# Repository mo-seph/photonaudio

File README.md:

# Quad LED Driver: audio over light

A four-channel analog LED driver for sending audio-rate signals through the air as light: soundcard → LED → air → phototransistor pickup → soundcard. Each channel is a linear voltage-controlled current sink (op-amp, transistor, sense resistor), so the light follows the signal rather than the LED's exponential V/I curve. Audio rides on an idle brightness set per channel by an on-board DAC or a trimmer. The design clips cleanly at off and at full when the input is overdriven, and the op-amp's supply rail sets a hard ceiling on LED current.

*Quad LED Driver Board v1.0 (November 2026): 170 × 100 mm, two layers. On the left is the 12 V input, the 5 V and 3.3 V supplies, and a XIAO ESP32-S3 with an MCP4728 four-channel DAC for the idle brightness. On the right are four identical channels A–D, each with a balanced audio input, DC lift, bias select (DAC or trimmer), amplifier, current sink and LED output.*

*The routing: top copper in red, bottom copper in blue, with the silkscreen. Each channel's current-sense return runs back separately to the star point at the main capacitor (the four diagonal tracks at bottom centre).*

## Status

- **v1.0 boards** arrived on 2026-11-17. Channel A, the supplies and the DAC are built and working, and channels B–D are next.
- **Channel A, measured** over a bench optical link (`measure/`): about 67 dB SNR unweighted (69 dB(A)) at 1% THD, with a −3 dB bandwidth of about 67 Hz to 20 kHz. The limit is the photosensor's distortion, not the driver.

## What's here

| Path | Contents |
|---|---|
| [OVERVIEW.md](OVERVIEW.md) | Goals and approach |
| [TUTORIAL.md](TUTORIAL.md) | How one channel works, part by part, with figures in `tutorial/` |
| [WORKING.md](WORKING.md) | Design notes, schematic and board reviews, measurement and bring-up log |
| [BRINGUP.md](BRINGUP.md) | Breadboard bring-up of one channel, power, XIAO and DAC |
| [build_plan/](build_plan/) | Staged build-and-test guide for the PCB (`index.html`, generated by `make_page.py`) |
| [BOM_pcb.md](BOM_pcb.md), [BOM_breadboard.md](BOM_breadboard.md) | Parts lists |
| [schematics/](schematics/) | Fusion Electronics (Eagle format) schematics and boards, PDF prints, and circuit drawings (`channel.png`, `dac.png`, `power.png`, `supply_filter.png`) |
| [cam_output/](cam_output/) | Gerbers as sent to JLCPCB for v1.0 |
| [fab/jlcpcb/](fab/jlcpcb/) | JLCPCB's CAM job and design rules for Fusion |
| [kicad/](kicad/) | The board converted to KiCad 10, checked against the Fusion original |
| [dac_test/](dac_test/) | Test firmware (PlatformIO) for the MCP4728 bias DAC |
| [measure/](measure/) | `linkmeasure`: frequency response, noise and distortion of the optical link, with every run's results |

In normal use, the board joins an I2C network of ESP32 devices as a Peripheral, with the four LED channels as one Element. That firmware lives in a separate repository.

Raw audio recordings from the measurements are not in the repository; each run keeps its analysed results (CSV, PNG, JSON).

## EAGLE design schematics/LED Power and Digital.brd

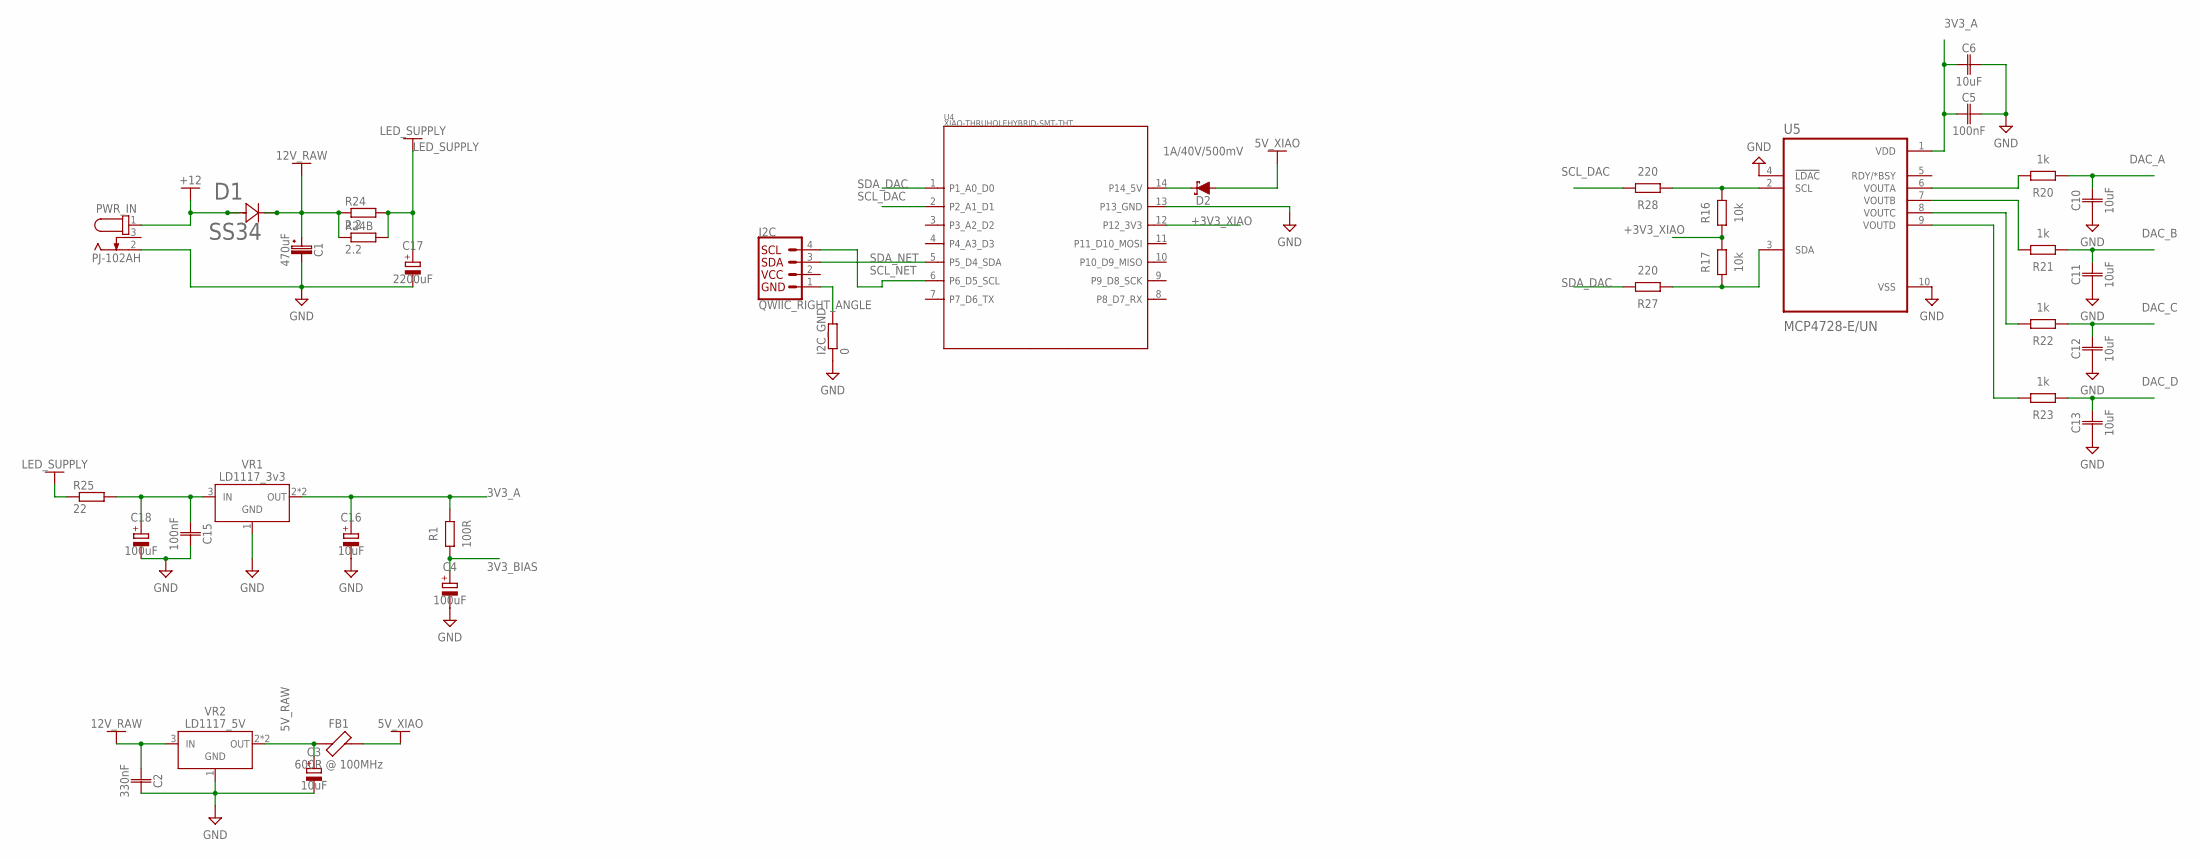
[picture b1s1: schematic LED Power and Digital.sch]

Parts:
C1: 470uF; CAPAE1030X1050N
C2: 330nF; CAPC2012X110
C3, C16: 10uF; A/3216-18W
C4, C18: 100uF; 153CLV-0605
C5, C15: 100nF; CAPC2012X110
C6, C10, C11, C12, C13: 10uF; CAPC3216X135
C17: 2200uF; E7,5-16
D1: SS34; DIODE_DO214AB
D2: 1A/40V/500mV; SMA-DIODE
FB1: 600R @ 100MHz; BEADC2012X105N
I2C: QWIIC_RIGHT_ANGLE; JST04_1MM_RA
I2C_GND: 0; R0805
PWR_IN: PJ-102AH
R1: 100R; RESC3216X70
R16, R17: 10k; RESC3216X70
R20, R21, R22, R23: 1k; RESC3216X70
R24, R24B: 2.2; R2512
R25: 22; R0805
R27, R28: 220; RESC3216X70
U4: XIAO-THRUHOLEHYBRID-SMT-THT; XIAO-GENERIC-HYBRID-MODULE14P-2.54-21X17.8MM
U5: MCP4728-E/UN; SOP50P490X110-10N
VR1: LD1117_3v3; SOT230P700X170-4
VR2: LD1117_5V; SOT230P700X170-4

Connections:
2: I2C.2
3V3_A: C5.1, C6.1, C16.+, R1.2, U5.1 (VDD), VR1.2 (VO), VR1.4 (VO)
3V3_BIAS: C4.+, R1.1
5V_RAW: C3.+, FB1.1, VR2.2 (VO), VR2.4 (VO)
5V_XIAO: D2.A, FB1.2
12V_RAW: C1.1 (+), C2.1, D1.1, R24.1, R24B.1, VR2.3 (VI); also elsewhere on the board
+3V3_XIAO: R16.1, R17.2, U4.12 (P12_3V3)
+12: D1.2, PWR_IN.1; also elsewhere on the board
DAC_A: C10.2, R20.1
DAC_B: C11.2, R21.1
DAC_C: C12.2, R22.1
DAC_D: C13.2, R23.1
GND: C1.2 (-), C2.2, C3.-, C4.-, C5.2, C6.2, C10.1, C11.1, C12.1, C13.1, C15.2, C16.-, C17.-, C18.-, I2C_GND.1, PWR_IN.2, U4.13 (P13_GND), U5.4 (!LDAC), U5.10 (VSS), VR1.1 (GND), VR2.1 (GND)
LED_SUPPLY: C17.+, R24.2, R24B.2, R25.1
unnamed: D2.C, U4.14 (P14_5V)
unnamed: I2C.1, I2C_GND.2
unnamed: C15.1, C18.+, R25.2, VR1.3 (VI)
unnamed: R16.2, R28.1, U5.2 (SCL)
unnamed: R17.1, R27.1, U5.3 (SDA)
unnamed: R20.2, U5.6 (VOUTA)
unnamed: R21.2, U5.7 (VOUTB)
unnamed: R22.2, U5.8 (VOUTC)
unnamed: R23.2, U5.9 (VOUTD)
SCL_DAC: R28.2, U4.2 (P2_A1_D1)
SCL_NET: I2C.4, U4.6 (P6_D5_SCL)
SDA_DAC: R27.2, U4.1 (P1_A0_D0)
SDA_NET: I2C.3, U4.5 (P5_D4_SDA)

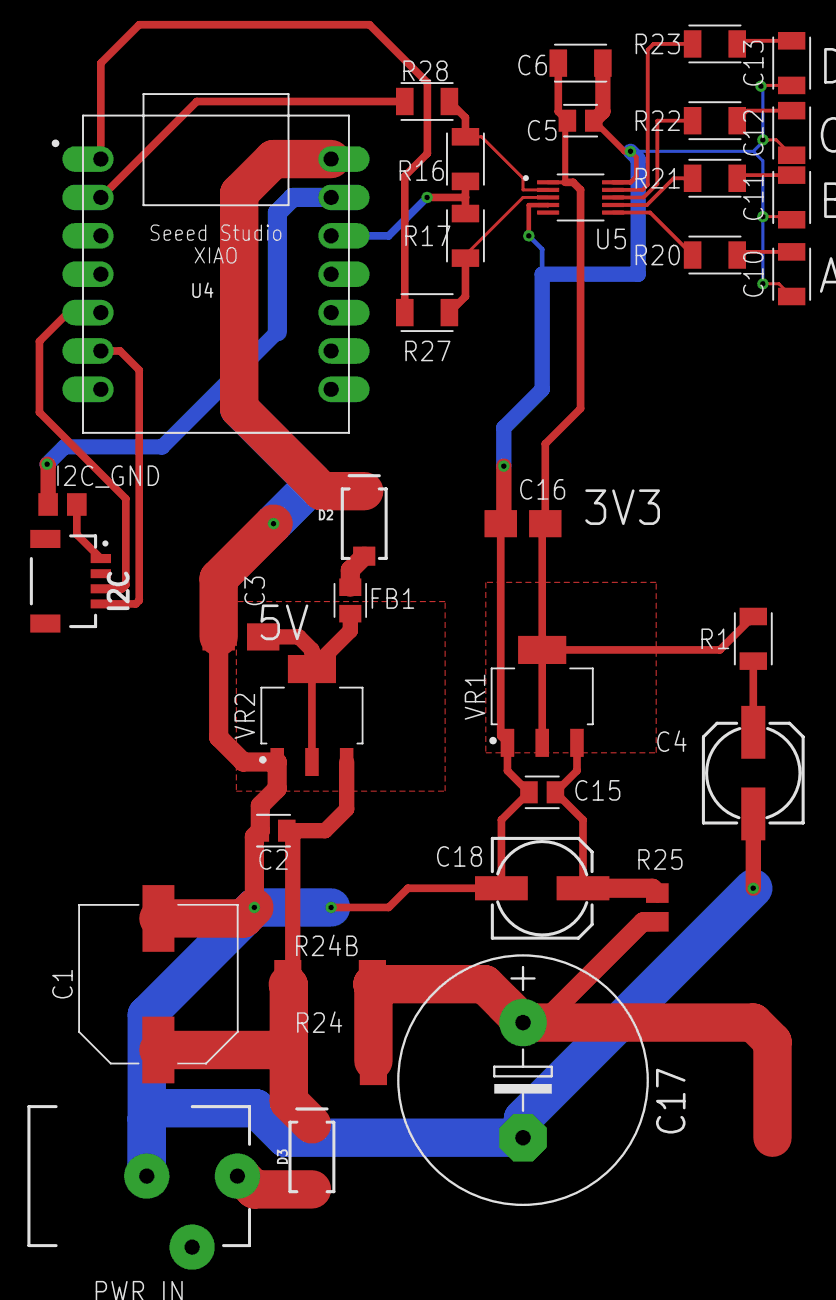
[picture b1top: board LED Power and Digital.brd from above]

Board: 2 copper layers, 36 parts (0 on the bottom side), 26 nets.

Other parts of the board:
D3: 3A/40V/500mV; SMA-DIODE

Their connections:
12V_RAW: D3.C; also elsewhere on the board
+12: D3.A; also elsewhere on the board

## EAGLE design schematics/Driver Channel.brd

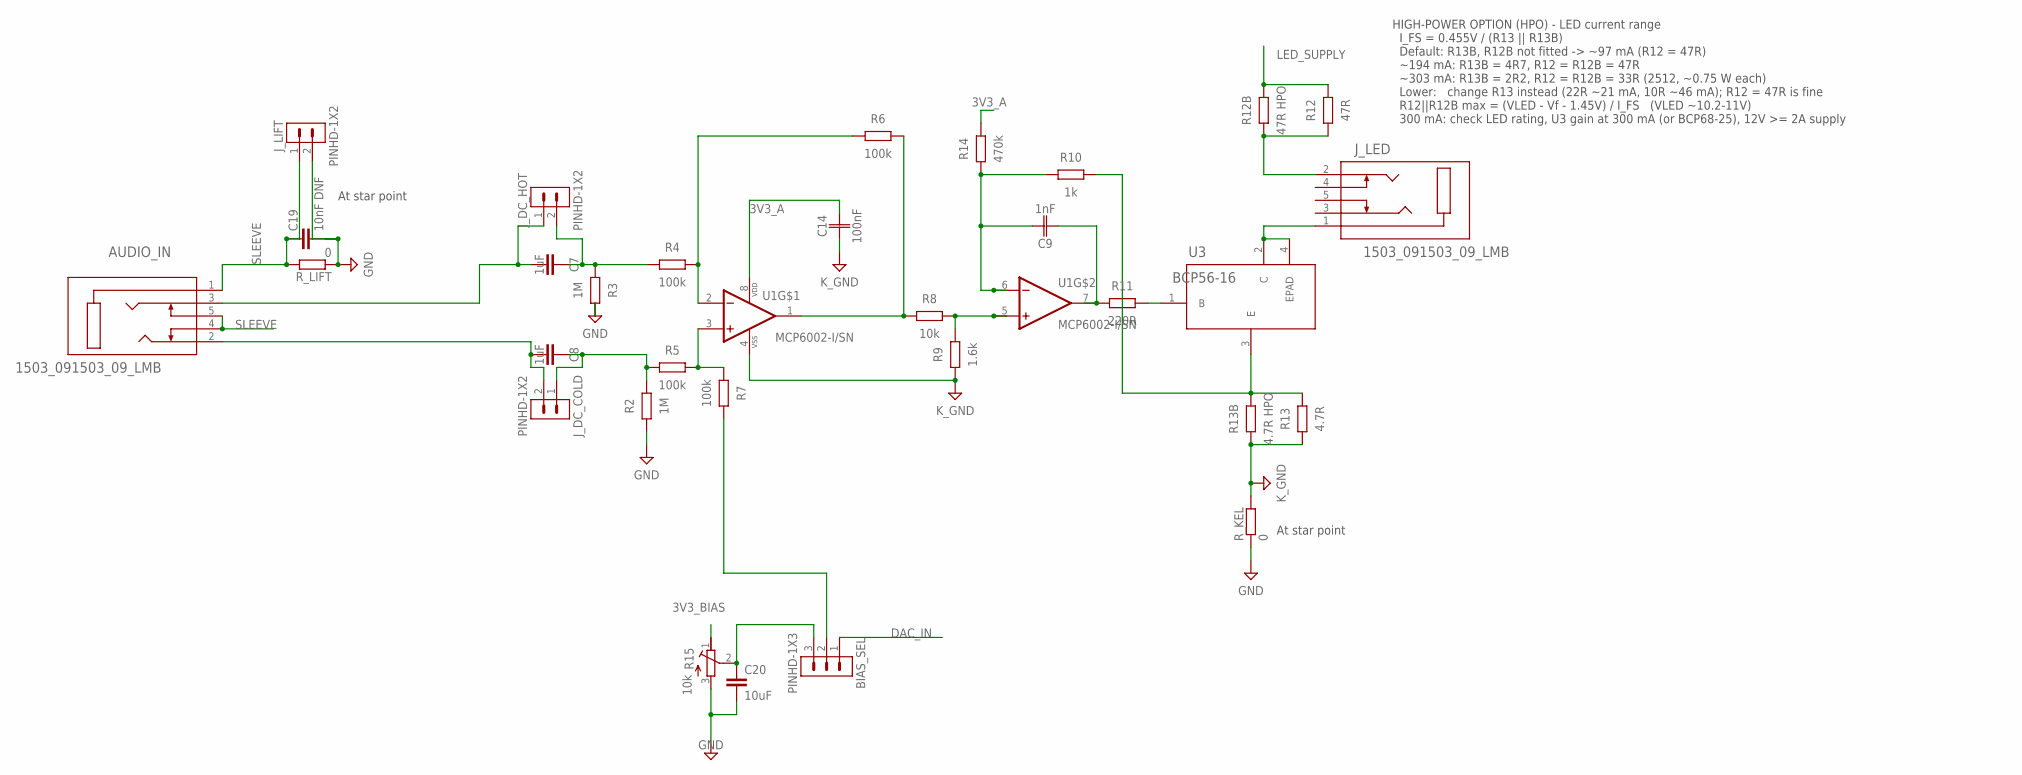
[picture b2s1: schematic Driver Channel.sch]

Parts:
AUDIO_IN: 1503_091503_09_LMB; 1503_09_LMB
BIAS_SEL: PINHD-1X3; 1X03
C7, C8: 1uF; C0805
C9: 1nF; CAPC2012X110
C14: 100nF; CAPC2012X110
C19: 10nF DNF; C0805
C20: 10uF; C0805
J_DC_COLD: PINHD-1X2; 1X02
J_DC_HOT: PINHD-1X2; 1X02
J_LED: 1503_091503_09_LMB; 1503_09_LMB
J_LIFT: PINHD-1X2; 1X02
R2, R3: 1M; RESC3216X70
R4, R5, R6, R7: 100k; RESC3216X70
R8: 10k; RESC3216X70
R9: 1.6k; RESC3216X70
R10: 1k; RESC3216X70
R11: 220R; RESC3216X70
R12: 47R; RESC6332X71
R12B: 47R HPO; RESC6332X71
R13: 4.7R; RESC3216X70
R13B: 4.7R HPO; RESC3216X70
R14: 470k; RESC3216X70
R15: 10k; RTRIM3314J
R_KEL: 0; R0805
R_LIFT: 0; R0805
U1: MCP6002-I/SN; SOIC127P600X175-8N
U3: BCP56-16; SOT-223_3P7X6P7_ONS

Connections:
3V3_A: C14.2, R14.2, U1.8 (VDD)
3V3_BIAS: R15.1 (E)
DAC_IN: BIAS_SEL.1
GND: C19.2, C20.2, J_LIFT.2, R2.1, R3.2, R15.3 (A), R_KEL.1, R_LIFT.1
K_GND: C14.1, R9.1, R13.1, R13B.1, R_KEL.2, U1.4 (VSS)
LED_SUPPLY: R12.2, R12B.2
unnamed: C8.1, J_DC_COLD.1, R2.2, R5.1
unnamed: C7.1, J_DC_HOT.2, R3.1, R4.1
unnamed: R4.2, R6.1, U1.2 (VINA-)
unnamed: R5.2, R7.1, U1.3 (VINA+)
unnamed: R6.2, R8.1, U1.1 (VOUTA)
unnamed: R8.2, R9.2, U1.5 (VINB+)
unnamed: R11.2, U3.1 (B)
unnamed: J_LED.1, U3.2 (C), U3.4 (EPAD)
unnamed: J_LED.2, R12.1, R12B.1
unnamed: R10.2, R13.2, R13B.2, U3.3 (E)
unnamed: C9.1, R11.1, U1.7 (VOUTB)
unnamed: C9.2, R10.1, R14.1, U1.6 (VINB-)
unnamed: BIAS_SEL.3, C20.1, R15.2 (S)
unnamed: AUDIO_IN.2, C8.2, J_DC_COLD.2
unnamed: AUDIO_IN.3, C7.2, J_DC_HOT.1
unnamed: BIAS_SEL.2, R7.2
SLEEVE: AUDIO_IN.1, AUDIO_IN.4, AUDIO_IN.5, C19.1, J_LIFT.1, R_LIFT.2

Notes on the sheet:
At star point
HIGH-POWER OPTION (HPO) - LED current range I_FS = 0.455V / (R13 || R13B) Default: R13B, R12B not fitted -> ~97 mA (R12 = 47R) ~194 mA: R13B = 4R7, R12 = R12B = 47R ~303 mA: R13B = 2R2, R12 = R12B = 33R (2512, ~0.75 W each) Lower: change R13 instead (22R ~21 mA, 10R ~46 mA); R12 = 47R is fine R12||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

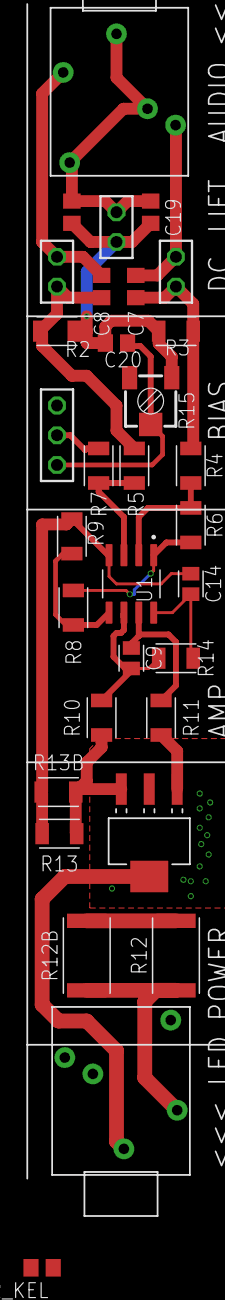
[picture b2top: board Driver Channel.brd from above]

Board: 2 copper layers, 32 parts (0 on the bottom side), 21 nets.

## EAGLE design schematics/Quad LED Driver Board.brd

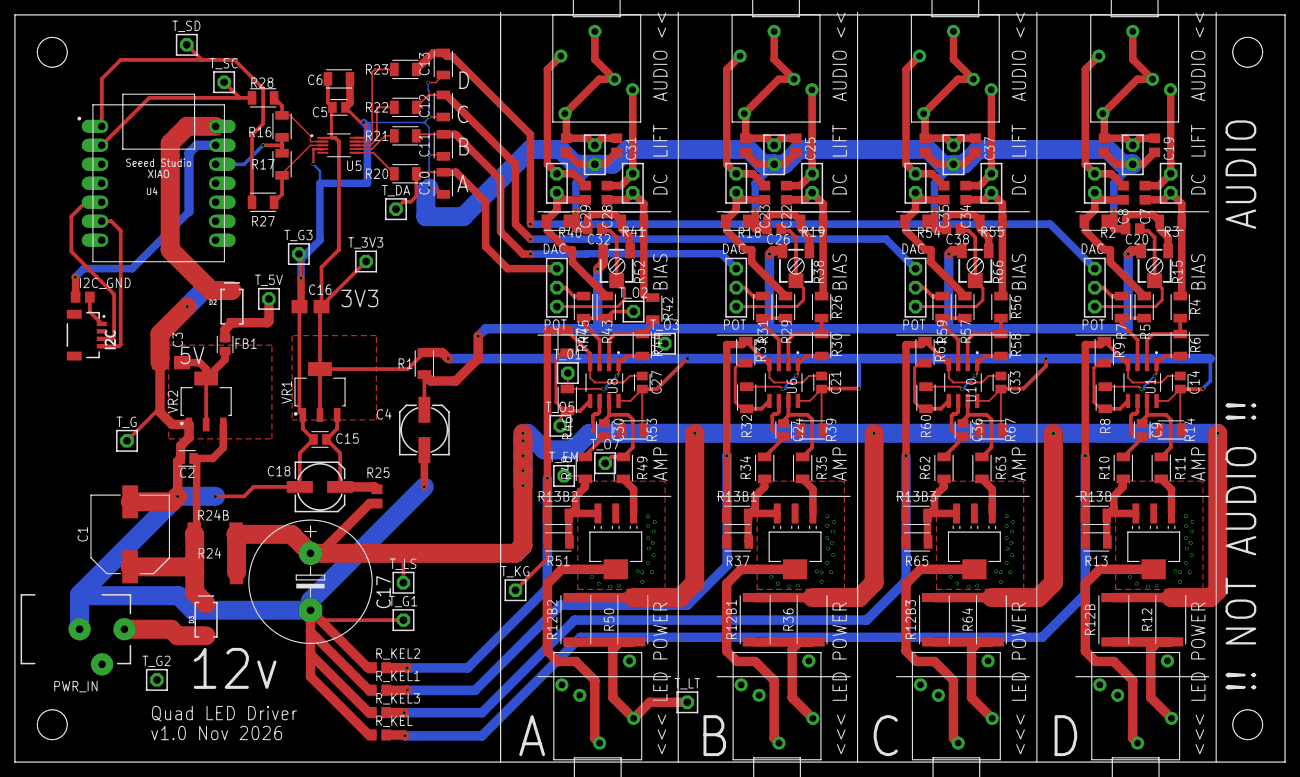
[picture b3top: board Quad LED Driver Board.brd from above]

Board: 2 copper layers, 170.0 x 100.0 mm, 182 parts (0 on the bottom side), 98 nets.

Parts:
AUDIO_IN, AUDIO_IN1, AUDIO_IN2, AUDIO_IN3: 1503_091503_09_LMB; 1503_09_LMB
BIAS_SEL, BIAS_SEL1, BIAS_SEL2, BIAS_SEL3: PINHD-1X3; 1X03
C1: 470uF; CAPAE1030X1050N
C2: 330nF; CAPC2012X110
C3, C16: 10uF; A/3216-18W
C4, C18: 100uF; 153CLV-0605
C5, C14, C15, C21, C27, C33: 100nF; CAPC2012X110
C6, C10, C11, C12, C13: 10uF; CAPC3216X135
C7, C8, C22, C23, C28, C29, C34, C35: 1uF; C0805
C9, C24, C30, C36: 1nF; CAPC2012X110
C17: 2200uF; E7,5-16
C19, C25, C31, C37: 10nF DNF; C0805
C20, C26, C32, C38: 10uF; C0805
D2: 1A/40V/500mV; SMA-DIODE
D3: 3A/40V/500mV; SMA-DIODE
FB1: 600R @ 100MHz; BEADC2012X105N
I2C: QWIIC_RIGHT_ANGLE; JST04_1MM_RA
I2C_GND: 0; R0805
J_DC_COLD, J_DC_COLD1, J_DC_COLD2, J_DC_COLD3: PINHD-1X2; 1X02
J_DC_HOT, J_DC_HOT1, J_DC_HOT2, J_DC_HOT3: PINHD-1X2; 1X02
J_LED, J_LED1, J_LED2, J_LED3: 1503_091503_09_LMB; 1503_09_LMB
J_LIFT, J_LIFT1, J_LIFT2, J_LIFT3: PINHD-1X2; 1X02
PWR_IN: PJ-102AH
R1: 100R; RESC3216X70
R2, R3, R18, R19, R40, R41, R54, R55: 1M; RESC3216X70
R4, R5, R6, R7, R26, R29, R30, R31, R42, R43, R44, R45, R56, R57, R58, R59: 100k; RESC3216X70
R8, R16, R17, R32, R46, R60: 10k; RESC3216X70
R9, R33, R47, R61: 1.6k; RESC3216X70
R10, R20, R21, R22, R23, R34, R48, R62: 1k; RESC3216X70
R11, R35, R49, R63: 220R; RESC3216X70
R12, R36, R50, R64: 47R; RESC6332X71
R12B, R12B1, R12B2, R12B3: 47R HPO; RESC6332X71
R13, R37, R51, R65: 4.7R; RESC3216X70
R13B, R13B1, R13B2, R13B3: 4.7R HPO; RESC3216X70
R14, R39, R53, R67: 470k; RESC3216X70
R15, R38, R52, R66: 10k; RTRIM3314J
R24, R24B: 2.2; R2512
R25: 22; R0805
R27, R28: 220; RESC3216X70
R_KEL, R_KEL1, R_KEL2, R_KEL3: 0; R0805
R_LIFT, R_LIFT1, R_LIFT2, R_LIFT3: 0; R0805
T_01, T_3V3, T_5V: PINHD-1X1; 1X01
T_DA: PINHD-1X1; 1X01
T_EM: PINHD-1X1; 1X01
T_G, T_G1, T_G2, T_G3: PINHD-1X1; 1X01
T_KG: PINHD-1X1; 1X01
T_LS: PINHD-1X1; 1X01
T_LT: PINHD-1X1; 1X01
T_O2, T_O3, T_O5, T_O7: PINHD-1X1; 1X01
T_SC: PINHD-1X1; 1X01
T_SD: PINHD-1X1; 1X01
U1, U6, U8, U10: MCP6002-I/SN; SOIC127P600X175-8N
U2, U3, U7, U9: BCP56-16; SOT-223_3P7X6P7_ONS
U4: XIAO-THRUHOLEHYBRID-SMT-THT; XIAO-GENERIC-HYBRID-MODULE14P-2.54-21X17.8MM
U5: MCP4728-E/UN; SOP50P490X110-10N
VR1: LD1117_3v3; SOT230P700X170-4
VR2: LD1117_5V; SOT230P700X170-4

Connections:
3V3_A: C5.1, C6.1, C14.2, C16.+, C21.2, C27.2, C33.2, R1.2, R14.2, R39.2, R53.2, R67.2, T_3V3.1, U1.8, U5.1, U6.8, U8.8, U10.8, VR1.2, VR1.4
3V3_BIAS: C4.+, R1.1, R15.1, R38.1, R52.1, R66.1
5V_RAW: C3.+, FB1.1, VR2.2, VR2.4
5V_XIAO: D2.A, FB1.2, T_5V.1
12V_RAW: C1.1, C2.1, D3.C, R24.1, R24B.1, VR2.3
+3V3_XIAO: R16.1, R17.2, U4.12
+12: D3.A, PWR_IN.1
DAC_A: BIAS_SEL2.1, C10.2, R20.1, T_DA.1
DAC_B: BIAS_SEL1.1, C11.2, R21.1
DAC_C: BIAS_SEL3.1, C12.2, R22.1
DAC_D: BIAS_SEL.1, C13.2, R23.1
GND: C1.2, C2.2, C3.-, C4.-, C5.2, C6.2, C10.1, C11.1, C12.1, C13.1, C15.2, C16.-, C17.-, C18.-, C19.2, C20.2, C25.2, C26.2, C31.2, C32.2, C37.2, C38.2, I2C_GND.1, J_LIFT.2, J_LIFT1.2, J_LIFT2.2, J_LIFT3.2, PWR_IN.2, R2.1, R3.2, R15.3, R18.1, R19.2, R38.3, R40.1, R41.2, R52.3, R54.1, R55.2, R66.3, R_KEL.1, R_KEL1.1, R_KEL2.1, R_KEL3.1, R_LIFT.1, R_LIFT1.1, R_LIFT2.1, R_LIFT3.1, T_G.1, T_G1.1, T_G2.1, T_G3.1, U4.13, U5.4, U5.10, VR1.1, VR2.1
K_GND_A: C27.1, R13B2.1, R47.1, R51.1, R_KEL2.2, T_KG.1, U8.4
K_GND_B: C21.1, R13B1.1, R33.1, R37.1, R_KEL1.2, U6.4
K_GND_C: C33.1, R13B3.1, R61.1, R65.1, R_KEL3.2, U10.4
K_GND_D: C14.1, R9.1, R13.1, R13B.1, R_KEL.2, U1.4
LED_SUPPLY: C17.+, R12.2, R12B.2, R12B1.2, R12B2.2, R12B3.2, R24.2, R24B.2, R25.1, R36.2, R50.2, R64.2, T_LS.1
unnamed: D2.C, U4.14
unnamed: I2C.1, I2C_GND.2
unnamed: C15.1, C18.+, R25.2, VR1.3
unnamed: C8.1, J_DC_COLD.1, R2.2, R5.1
unnamed: C7.1, J_DC_HOT.2, R3.1, R4.1
unnamed: R4.2, R6.1, U1.2
unnamed: R5.2, R7.1, U1.3
unnamed: R6.2, R8.1, U1.1
unnamed: R8.2, R9.2, U1.5
unnamed: R11.2, U3.1
unnamed: J_LED.2, R12.1, R12B.1
unnamed: R10.2, R13.2, R13B.2, U3.3
unnamed: C9.1, R11.1, U1.7
unnamed: C9.2, R10.1, R14.1, U1.6
unnamed: AUDIO_IN.2, C8.2, J_DC_COLD.2
unnamed: BIAS_SEL.2, R7.2
unnamed: AUDIO_IN.3, C7.2, J_DC_HOT.1
unnamed: BIAS_SEL.3, C20.1, R15.2
unnamed: J_LED.1, U3.4
unnamed: C23.1, J_DC_COLD1.1, R18.2, R29.1
unnamed: R16.2, R28.1, U5.2
unnamed: R17.1, R27.1, U5.3
unnamed: R20.2, U5.6
unnamed: R21.2, U5.7
unnamed: R22.2, U5.8
unnamed: R23.2, U5.9
unnamed: C22.1, J_DC_HOT1.2, R19.1, R26.1
unnamed: R26.2, R30.1, U6.2
unnamed: R29.2, R31.1, U6.3
unnamed: R30.2, R32.1, U6.1
unnamed: R32.2, R33.2, U6.5
unnamed: R35.2, U2.1
unnamed: J_LED1.2, R12B1.1, R36.1
unnamed: R13B1.2, R34.2, R37.2, U2.3
unnamed: C24.1, R35.1, U6.7
unnamed: C24.2, R34.1, R39.1, U6.6
unnamed: AUDIO_IN1.2, C23.2, J_DC_COLD1.2
unnamed: BIAS_SEL1.2, R31.2
unnamed: AUDIO_IN1.3, C22.2, J_DC_HOT1.1
unnamed: BIAS_SEL1.3, C26.1, R38.2
unnamed: J_LED1.1, U2.4
unnamed: C29.1, J_DC_COLD2.1, R40.2, R43.1
unnamed: C28.1, J_DC_HOT2.2, R41.1, R42.1
unnamed: R42.2, R44.1, T_O3.1, U8.2
unnamed: R43.2, R45.1, T_O2.1, U8.3
unnamed: R44.2, R46.1, T_01.1, U8.1
unnamed: R46.2, R47.2, T_O5.1, U8.5
unnamed: R49.2, U7.1
unnamed: J_LED2.2, R12B2.1, R50.1, T_LT.1
unnamed: R13B2.2, R48.2, R51.2, T_EM.1, U7.3
unnamed: C30.1, R49.1, T_O7.1, U8.7
unnamed: C30.2, R48.1, R53.1, U8.6
unnamed: AUDIO_IN2.2, C29.2, J_DC_COLD2.2
unnamed: BIAS_SEL2.2, R45.2
unnamed: AUDIO_IN2.3, C28.2, J_DC_HOT2.1
unnamed: BIAS_SEL2.3, C32.1, R52.2
unnamed: J_LED2.1, U7.4
unnamed: C35.1, J_DC_COLD3.1, R54.2, R57.1
unnamed: C34.1, J_DC_HOT3.2, R55.1, R56.1
unnamed: R56.2, R58.1, U10.2
unnamed: R57.2, R59.1, U10.3
unnamed: R58.2, R60.1, U10.1
unnamed: R60.2, R61.2, U10.5
unnamed: R63.2, U9.1
unnamed: J_LED3.2, R12B3.1, R64.1
unnamed: R13B3.2, R62.2, R65.2, U9.3
unnamed: C36.1, R63.1, U10.7
unnamed: C36.2, R62.1, R67.1, U10.6
unnamed: AUDIO_IN3.2, C35.2, J_DC_COLD3.2
unnamed: BIAS_SEL3.2, R59.2
unnamed: AUDIO_IN3.3, C34.2, J_DC_HOT3.1
unnamed: BIAS_SEL3.3, C38.1, R66.2
unnamed: J_LED3.1, U9.4
SCL_DAC: R28.2, T_SC.1, U4.2
SCL_NET: I2C.4, U4.6
SDA_DAC: R27.2, T_SD.1, U4.1
SDA_NET: I2C.3, U4.5
SLEEVE_A: AUDIO_IN2.1, AUDIO_IN2.4, AUDIO_IN2.5, C31.1, J_LIFT2.1, R_LIFT2.2
SLEEVE_B: AUDIO_IN1.1, AUDIO_IN1.4, AUDIO_IN1.5, C25.1, J_LIFT1.1, R_LIFT1.2
SLEEVE_C: AUDIO_IN3.1, AUDIO_IN3.4, AUDIO_IN3.5, C37.1, J_LIFT3.1, R_LIFT3.2
SLEEVE_D: AUDIO_IN.1, AUDIO_IN.4, AUDIO_IN.5, C19.1, J_LIFT.1, R_LIFT.2

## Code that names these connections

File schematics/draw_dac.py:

"""DAC section, 3.3 V analog version (2026-10-23): XIAO + MCP4728 + output smoothing.
The DAC runs from +3V3_A, so it talks to the XIAO directly - no level shifter (Q2, Q3, R18, R19 removed;
R16/R17 stay as the 4.7k bus pull-ups).
Designators follow 'LED Driver.sch'. BIAS_SEL pin 1 <- DAC_x is the intended wiring.
Power rails are shown as net labels (open dots) rather than drawn wires.
v1 (2026-11-04, from the DAC update-noise tests; new / changed parts in orange):
  C10-C13 1 µF -> 10 µF (16 Hz: zipper noise from ramps −13 dB, measured);
  R16/R17 4.7k to +3V3_A -> 10k to the XIAO's 3V3 (pull-up current off the analog rail);
  R27/R28 220 Ω in series at the XIAO's SDA/SCL pins.
Run: python draw_dac.py -> dac.svg / dac.png"""
import schemdraw
import schemdraw.elements as elm
from schemdraw.elements import IcPin

PIN = 1.5  # pin spacing, so the bus rows line up with the DAC pins
NEW = '#c2410c'   # new / changed for v1

with schemdraw.Drawing(show=False) as d:
    d.config(bgcolor='#fcfcfb', margin=0.6, fontsize=11, unit=2.0)

    # ---- U4: XIAO ESP32-S3 -------------------------------------------------------------
    xiao = elm.Ic(pins=[
        IcPin(name='5V', side='top', slot='1/2'),
        IcPin(name='3V3', side='top', slot='2/2', anchorname='V33'),
        IcPin(name='GND', side='bottom'),
        IcPin(name='D4 (GPIO5)', side='left', slot='2/2', anchorname='D4'),
        IcPin(name='D5 (GPIO6)', side='left', slot='1/2', anchorname='D5'),
        IcPin(name='D0 (GPIO1)', side='right', slot='2/2', anchorname='D0'),
        IcPin(name='D1 (GPIO2)', side='right', slot='1/2', anchorname='D1'),
    ], size=(5.5, 3.5), pinspacing=PIN, leadlen=0.6)

    elm.Line().at(xiao['5V']).up(1.0)
    elm.Dot(open=True).label('XIAO_5V', 'left')
    elm.Line().at(xiao.V33).up(1.0).color(NEW)
    elm.Dot(open=True).label('XIAO_3V3 (output)', 'right').color(NEW)
    elm.Line().at(xiao.GND).down(0.5)
    elm.Ground()
    elm.Label().at((xiao.GND[0] + 0.4, xiao.GND[1] - 0.3)).label('U4  XIAO ESP32-S3', fontsize=11, halign='left')

    # Network I2C to the Central (Wire, slave) on connector J2
    elm.Line().at(xiao.D4).left(2.0)
    elm.Dot(open=True).label('J2 SDA_NET', 'left')
    elm.Line().at(xiao.D5).left(2.0)
    elm.Dot(open=True).label('J2 SCL_NET', 'left')
    elm.Dot(open=True).at((xiao.D5[0] - 2.0, xiao.D5[1] - 1.5)).label('J2 GND', 'left')
    elm.Ground()

    # ---- DAC bus (Wire1), 3.3 V on both sides: 220 Ω series at the XIAO, 10k pull-ups to the XIAO's 3V3 ----
    elm.Resistor().at(xiao.D0).right().label('R27 220Ω', loc='top', fontsize=10).color(NEW)
    elm.Line().right(0.5)
    sda = elm.Dot()
    elm.Resistor().at(sda.center).up().label('R17 10k', loc='bottom', fontsize=10).color(NEW)
    elm.Dot(open=True).label('XIAO_3V3', 'top', fontsize=10).color(NEW)
    elm.Line().at(sda.center).right(4.5)
    elm.Label().at((sda.center[0] + 1.0, sda.center[1] + 0.3)).label('SDA_DAC', fontsize=9, halign='left')
    sda_end = d.here

    elm.Resistor().at(xiao.D1).right().label('R28 220Ω', loc='bottom', fontsize=10).color(NEW)
    elm.Line().right(2.0)
    scl = elm.Dot()
    elm.Resistor().at(scl.center).down().label('R16 10k', loc='top', fontsize=10).color(NEW)
    elm.Dot(open=True).label('XIAO_3V3', 'bottom', fontsize=10).color(NEW)
    elm.Line().at(scl.center).right(3.0)
    elm.Label().at((scl.center[0] + 0.5, scl.center[1] + 0.3)).label('SCL_DAC', fontsize=9, halign='left')

    # ---- U5: MCP4728 ---------------------------------------------------------------------
    dac = elm.Ic(pins=[
        IcPin(name='VDD', pin='1', side='top'),
        IcPin(name='SDA', pin='3', side='left', slot='4/4'),
        IcPin(name='SCL', pin='2', side='left', slot='3/4'),
        IcPin(name='~LDAC', pin='4', side='left', slot='2/4', anchorname='LDAC'),
        IcPin(name='RDY/~BSY', pin='5', side='left', slot='1/4', anchorname='RDY'),
        IcPin(name='VOUTA', pin='6', side='right', slot='4/4'),
        IcPin(name='VOUTB', pin='7', side='right', slot='3/4'),
        IcPin(name='VOUTC', pin='8', side='right', slot='2/4'),
        IcPin(name='VOUTD', pin='9', side='right', slot='1/4'),
        IcPin(name='VSS', pin='10', side='bottom'),
    ], size=(4.5, 6.5), pinspacing=PIN, leadlen=0.6).anchor('SDA').at(sda_end) \
        .label('U5\nMCP4728', 'center', fontsize=11)

    elm.Line().at(dac.LDAC).left(1.0)
    elm.Ground().label('tied low', 'bottom', fontsize=9)
    elm.Line().at(dac.RDY).left(1.0)
    elm.Label().label('NC', loc='left', fontsize=9)
    elm.Line().at(dac.VSS).down(0.5)
    elm.Ground()

    # VDD from the clean analog 3.3 V, decoupled right at the pin
    elm.Line().at(dac.VDD).up(3.5)
    vdd = elm.Dot()
    elm.Dot(open=True).at((vdd.center[0], vdd.center[1] + 0.6)).label('+3V3_A', 'top')
    elm.Line().at(vdd.center).up(0.6)
    elm.Line().at(vdd.center).right(1.5)
    elm.Dot()
    d.push(); elm.Capacitor().down().label('C5\n100nF', loc='bottom', fontsize=10); elm.Ground(); d.pop()
    elm.Line().right(1.5)
    elm.Capacitor().down().label('C6\n10µF', loc='bottom', fontsize=10)
    elm.Ground()

    # ---- Output smoothing, fanned out so the caps don't cross other outputs ------------------
    jogs = {'VOUTA': 3.0, 'VOUTB': 0.75, 'VOUTC': -0.75, 'VOUTD': -3.0}
    for i, (pin, ch) in enumerate([('VOUTA', 'A'), ('VOUTB', 'B'), ('VOUTC', 'C'), ('VOUTD', 'D')]):
        p = dac.absanchors[pin]
        elm.Line().at(p).right(0.5)
        elm.Line().toy(p[1] + jogs[pin])
        elm.Line().right(0.5)
        elm.Resistor().right().label(f'R{20 + i} 1k', fontsize=10)
        n = elm.Dot()
        elm.Line().right(2.0)
        elm.Dot(open=True).label(f'DAC_{ch} → channel {ch}, BIAS_SEL pin 1', 'right', fontsize=10)
        elm.Capacitor().at(n.center).down().label(f'C{10 + i} 10µF', loc='bottom', fontsize=10).color(NEW)
        elm.Ground()

    elm.Label().at((dac.VSS[0], dac.VSS[1] - 6.0)).label(
        'MCP4728 (MSOP-10): default I2C address 0x60, on the XIAO\'s second I2C bus (Wire1: D0 = SDA, D1 = SCL)\n'
        'Runs from +3V3_A, same as the XIAO\'s logic: no level shifter needed.  ~LDAC tied low\n'
        'Reference = VDD (set in firmware) → DAC_x = 0–3.3 V, same range as the trimmer and the U1A clamp → full current.\n'
        '    Internal 2.048 V reference also works: 0.5 mV steps (≈ −5 dB zipper); the bias then tops out at 62% of full scale\n'
        'Smoothing: 1k + 10µF ≈ 16 Hz (ramp zipper −13 dB). R kept at 1k so it barely upsets the difference amp\'s 100k balance\n'
        'Each DAC write adds a click (500 writes/s = a 500 Hz comb): firmware writes only when the value changes.\n'
        'Layout: SDA/SCL short, over unbroken ground, away from J1 / U1A / Vbias / R13; C5/C6 at U5\'s pins;\n'
        '    XIAO / U5 ground returns kept local. XIAO off USB in use (a USB loop adds hum; use a USB isolator for development)',
        fontsize=10)

    d.save('dac.svg', transparent=False)
    d.save('dac.png', transparent=False, dpi=150)

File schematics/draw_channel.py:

"""One LED driver channel (two op-amp version), 3.3 V analog supply (2026-10-23).
Designators match 'LED Driver.sch'. Changes from the 5 V version: U1, R14 and the trimmer
run from 3.3 V; R9 1k -> 1.6k; R14 1M -> 470k.
v1 (2026-11-03): C9 100 pF -> 1 nF (as on the breadboard: more phase margin, no audio effect);
J1 sleeve to GND through a ground-lift footprint, R26 (0 Ω, or 100 Ω with C19 10 nF across it).
2026-11-04, up to 300 mA LEDs: R13B in parallel with R13 sets the range (not fitted = 97 mA, 2.2 Ω = 303 mA);
R12B in parallel with R12 shares the heat; R11 470 -> 220 Ω for the base current; C20 10 µF at the trimmer
wiper (keeps Vbias low-impedance at hum frequencies, like C10 does for the DAC).
New / changed parts in orange.
Run: python draw_channel.py -> channel.svg / channel.png"""
import schemdraw
import schemdraw.elements as elm

NEW = '#c2410c'   # new / changed for v1


def pin_label(at, text, dx=0.0, dy=0.3):
    elm.Label().at((at[0] + dx, at[1] + dy)).label(text, fontsize=8)


with schemdraw.Drawing(show=False) as d:
    d.config(bgcolor='#fcfcfb', margin=0.6, fontsize=11, unit=2.2)

    # ---- U1A: balanced difference amp, reference = Vbias --------------------------
    # flip(): + (in2) on top, − (in1) on bottom
    op1 = elm.Opamp(leads=True).flip().label('U1A', loc='center', ofst=(-0.3, 0), fontsize=10)
    pin_label(op1.in2, 'pin 3')
    pin_label(op1.in1, 'pin 2', dy=-0.6)
    pin_label(op1.out, 'pin 1', dx=-0.6)

    # Tip (hot) -> C8 -> R5 -> +   (R2 = 1M bleed)
    elm.Line().at(op1.in2).left(0.75)
    np = elm.Dot()
    elm.Resistor().left().label('R5 100k')
    elm.Dot()
    d.push(); elm.Resistor().down().label('R2 1M', loc='bottom'); elm.Ground(); d.pop()
    elm.Capacitor().left().label('C8 1µF\n(JP4 across = DC)')
    elm.Dot(open=True).label('J1 tip', 'left')

    # + input also goes via R7 to Vbias (JP3 centre pin)
    elm.Resistor().at(np.center).up().label('R7 100k', loc='bottom')
    vb = elm.Dot().label('Vbias', 'left')

    # Ring (cold) -> C7 -> R4 -> −   (R3 = 1M bleed)
    elm.Line().at(op1.in1).left(0.75)
    nn = elm.Dot()
    elm.Line().down(2.2)
    elm.Resistor().left().label('R4 100k', loc='bottom')
    elm.Dot()
    d.push(); elm.Resistor().down().label('R3 1M', loc='bottom'); elm.Ground(); d.pop()
    elm.Capacitor().left().label('C7 1µF\n(JP5 across = DC)')
    ring = elm.Dot(open=True).label('J1 ring', 'left')
    elm.Dot(open=True).at((ring.center[0], ring.center[1] - 2.5)).label('J1 sleeve', 'left')
    # Ground-lift footprint: 0 Ω normally; 100 Ω ∥ 10 nF breaks a hum loop through the cable shield
    elm.Line().down(1.0)
    lift = elm.Dot()
    elm.Resistor().down().label('R26 0Ω\n(100Ω to lift)', loc='top')
    lifted = elm.Dot()
    elm.Ground()
    elm.Line().at(lift.center).right(1.5)
    elm.Capacitor().down().label('C19 10nF\n(only with 100Ω)', loc='bottom')
    elm.Line().tox(lifted.center)
    elm.Label().at((ring.center[0] - 2.6, ring.center[1] - 8.6)).label(
        'J1 tip and ring switch (NC) pins → the J1 sleeve net (above R26):\n'
        'an unplugged input is shorted, so the channel idles silently.\n'
        'Sleeve switch pin: not connected', fontsize=9, halign='left').color(NEW)

    # Feedback: R6 from output to − input
    elm.Line().at(nn.center).down(1.1)
    elm.Resistor().right().tox(op1.out).label('R6 100k', loc='bottom')
    elm.Line().toy(op1.out)

    # ---- Bias select: BIAS_SEL (3-pin jumper) picks trimmer R15 or the DAC -------------
    elm.Line().at(vb.center).up(0.6)
    sw = elm.SwitchSpdt2(action=None).up().anchor('a')
    elm.Label().at((sw.a[0] - 0.4, sw.a[1] + 0.4)).label(
        'BIAS_SEL (3-pin jumper)\n1 = DAC\n2 = Vbias\n3 = trimmer', fontsize=9, halign='right')
    # right throw -> trimmer wiper
    elm.Line().at(sw.c).up(0.6)
    elm.Line().right(1.0)
    elm.Dot().color(NEW)
    d.push(); elm.Capacitor().down().label('C20\n10µF', loc='bottom', fontsize=10).color(NEW); elm.Ground(); d.pop()
    elm.Line().right(1.0)
    pot = elm.Potentiometer().up().anchor('tap').label('R15 10k\ntrimmer', loc='bottom')
    elm.Line().at(pot.end).up(0.3)
    elm.Dot(open=True).label('+3V3_BIAS', 'right')
    elm.Ground().at(pot.start)
    # left throw -> DAC output
    elm.Line().at(sw.b).up(1.4)
    elm.Dot(open=True).label('DAC_A (B, C, D on\nthe other channels)', 'left')

    # ---- Divider R8/R9 -----------------------------------------------------------------
    elm.Line().at(op1.out).right(0.5)
    elm.Dot().label('V1', 'bottom', fontsize=10)
    elm.Resistor().right().label('R8 10k')
    elm.Dot().label('Vctrl', 'top', fontsize=10)
    d.push(); elm.Resistor().down().label('R9 1.6k', loc='top'); elm.Ground(); d.pop()
    elm.Line().right(1)

    # ---- U1B + Q1: current sink -------------------------------------------------------
    op2 = elm.Opamp(leads=True).flip().anchor('in2').label('U1B', loc='center', ofst=(-0.3, 0), fontsize=10)
    pin_label(op2.in2, 'pin 5')
    pin_label(op2.in1, 'pin 6', dy=-0.6)
    pin_label(op2.out, 'pin 7', dx=-0.6)
    elm.Resistor().at(op2.out).right().label('R11 220Ω', color=NEW).color(NEW)
    q1 = elm.BjtNpn().anchor('base').label('U3\nBCP56-16\n(tab = C)', 'right')

    # Collector -> LED (off-board on JP2) -> R12 ∥ R12B -> LED_SUPPLY
    elm.LED().at(q1.collector).up().reverse().label('LED connector\npin 1 = anode\npin 2 = cathode', loc='bottom', fontsize=9)
    r12 = elm.Resistor().up().label('R12 47Ω\n2512 1W', loc='bottom')
    elm.Dot(open=True).label('LED_SUPPLY', 'right')
    elm.Dot().at(r12.start).color(NEW)
    elm.Line().at(r12.start).left(1.8).color(NEW)
    elm.Resistor().up().label('R12B\n(not fitted;\n300 mA: both 33Ω)', loc='top', fontsize=9).color(NEW)
    elm.Line().right(1.8).color(NEW)
    elm.Dot().at(r12.end).color(NEW)

    # Emitter -> R13 ∥ R13B -> GND (R13B sets the range)
    elm.Line().at(q1.emitter).down(0.5)
    ne = elm.Dot()
    elm.Line().down(0.5)
    r13 = elm.Resistor().down().label('R13 4.7Ω\n1206', loc='bottom')
    elm.Ground()
    elm.Dot().at(r13.start).color(NEW)
    elm.Line().at(r13.start).right(2.8).color(NEW)
    elm.Resistor().down().label('R13B (not fitted)\nsets the range:\n2.2Ω → 303 mA', loc='bottom', fontsize=9).color(NEW)
    elm.Line().left(2.8).color(NEW)
    elm.Dot().at(r13.end).color(NEW)

    # R10 emitter -> − input, C9 output -> − input
    elm.Line().at(op2.in1).left(0.5)
    elm.Dot()
    elm.Line().down(1.0)
    elm.Dot()
    d.push()
    elm.Capacitor().right().tox(op2.out).label('C9 1nF', loc='bottom', fontsize=10)
    elm.Line().toy(op2.out)
    elm.Dot()
    d.pop()
    elm.Line().down(1.6)
    corner = elm.Dot()
    elm.Resistor().right().tox(ne.center[0] - 1.2).label('R10 1k', loc='bottom')
    elm.Line().toy(ne.center)
    elm.Line().tox(ne.center)

    # R14: lifts pin 6 by ~7 mV so a zero command turns U3 fully off (beats the op-amp's offset)
    elm.Resistor().at(corner.center).down().label('R14 470k', loc='top')
    elm.Dot(open=True).label('+3V3_A', 'bottom')

    # ---- U1 power pins ------------------------------------------------------------------
    bx, by = op1.out[0] - 2, op1.out[1] - 8.0
    elm.Dot(open=True).at((bx, by)).label('+3V3_A → U1 pin 8', 'left')
    elm.Capacitor().down().label('C14\n100nF', loc='bottom')
    elm.Ground().label('U1 pin 4', 'left', ofst=0.6)

    elm.Label().at((op2.out[0] + 0.5, by - 0.5)).label(
        'V1 = Vbias + (tip − ring), clipped to 0–3.3 V by U1\n'
        'Vctrl = V1 × R9/(R8+R9) = V1 / 7.25  (3.3 V → 0.455 V)\n'
        'I_LED = (Vctrl − 7 mV) / (R13 ∥ R13B)  (≈ 95 mA max; R13B 2.2Ω → ≈ 300 mA)\n'
        'R14 adds the 7 mV, so a zero command really is off\n'
        'U1 must be MCP6002 (an LM358 can\'t run on 3.3 V).\n'
        'Audio full swing: ±1.65 V peak around mid bias\n'
        'Kelvin: take U1\'s ground (pin 4, R9, C14) from R13\'s bottom pad;\n'
        'route the LED return from there to the power entry on its own',
        fontsize=10)

    d.save('channel.svg', transparent=False)
    d.save('channel.png', transparent=False, dpi=150)

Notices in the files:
parts and their libraries:
COPYRIGHT: Copyright (C) 2026 Ultra Librarian. All rights reserved.
SparkFun-DiscreteSemi: Licensing: Creative Commons ShareAlike 4.0 International - https://creativecommons.org/licenses/by-sa/4.0
